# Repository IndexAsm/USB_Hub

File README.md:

# USB Hub

## Overview
A 4 port USB Hub.

## USB Version
It support USB 2.0 and older

## Max Current
It can supply up to 500mA per port <b>only when powered from USB-C compatible supply</b>. If the host port is connected to USB-A via USB-A USB-C cable it will only supply 100mA per port, to not exceed 500mA total.

## Hardware

It has a USB-C input and 4 USB-A output ports. Every port has ESD protection.

It uses USB2514 as the main IC.

Everything is placed on a 4-layer board.

## BOM

| Reference                                                                | Qty | Value            | Link                                                                                             | Footprint                                              |
|--------------------------------------------------------------------------|-----|------------------|--------------------------------------------------------------------------------------------------|--------------------------------------------------------|
| C1,C3,C4,C6,C7,C8,C9,C10,C11,C12,C13,C17,C18,C22,C23,C24,C25,C28,C29,C44 | 20  | 100n             |                                                                                                  | Capacitor_SMD:C_0603_1608Metric                        |
| C2,C5,C14,C15,C16,C19,C20,C21,C30                                        | 9   | 2u2              |                                                                                                  | Capacitor_SMD:C_0603_1608Metric                        |
| C34,C35                                                                  | 2   | 8p               | https://www.tme.eu/pl/details/cga3e2c0g1h080daa/kondensatory-mlcc-smd/tdk/cga3e2c0g1h080d080aa/  | Capacitor_SMD:C_0603_1608Metric                        |
| C57,C58                                                                  | 2   | 22u              | https://www.tme.eu/pl/details/grm31cr61e226ke15l/kondensatory-mlcc-smd/murata/                   | Capacitor_SMD:C_1206_3216Metric                        |
| J1,J2,J3,J4                                                              | 4   | USB_A            |                                                                                                  | USB-A-S-X-X-VT:USB-A-S-X-X-VT                          |
| J12                                                                      | 1   | USB4105-GF-A-120 | https://www.tme.eu/pl/details/usb4105-gf-a-120/zlacza-usb-i-ieee1394/gct/                        | Connector_USB:USB_C_Receptacle_G-Switch_GT-USB-7010ASV |
| R1,R2,R3,R4,R5,R6,R7,R8,R9,R10,R11                                       | 11  | 100k             |                                                                                                  | Resistor_SMD:R_0603_1608Metric                         |
| R12                                                                      | 1   | 12k              |                                                                                                  | Resistor_SMD:R_0603_1608Metric                         |
| R33,R34                                                                  | 2   | 5k1              |                                                                                                  | Resistor_SMD:R_0603_1608Metric                         |
| R36                                                                      | 1   | 1M               |                                                                                                  | Resistor_SMD:R_0603_1608Metric                         |
| U1                                                                       | 1   | USB2514B_Bi      | https://www.tme.eu/pl/details/usb2514b-aezc/uklady-scalone-interfejs-usb/microchip-technology/   | Package_DFN_QFN:QFN-36-1EP_6x6mm_P0.5mm_EP3.7x3.7mm    |
| U2,U3                                                                    | 2   | MIC2026-1xM      | https://www.tme.eu/pl/details/mic2026-1ym/power-switches-uklady-scalone/microchip-technology/    | Package_SO:SOIC-8_3.9x4.9mm_P1.27mm                    |
| U4,U5,U6,U7,U8                                                           | 5   | USBLC6-2SC6      |                                                                                                  | Package_TO_SOT_SMD:SOT-23-6                            |
| U9                                                                       | 1   | AMS1117-3.3      |                                                                                                  | Package_TO_SOT_SMD:SOT-223-3_TabPin2                   |
| Y1                                                                       | 1   | Crystal_GND24    | https://www.tme.eu/pl/en/details/3225-24m-sr/resonators-and-generators/sr-passives/wtl3m23500rh/ | Crystal:Crystal_SMD_EuroQuartz_MT-4Pin_3.2x2.5mm       |
| PCB                                                                      | 1   |                  | https://jlcpcb.com/                                                                              |                                                        |

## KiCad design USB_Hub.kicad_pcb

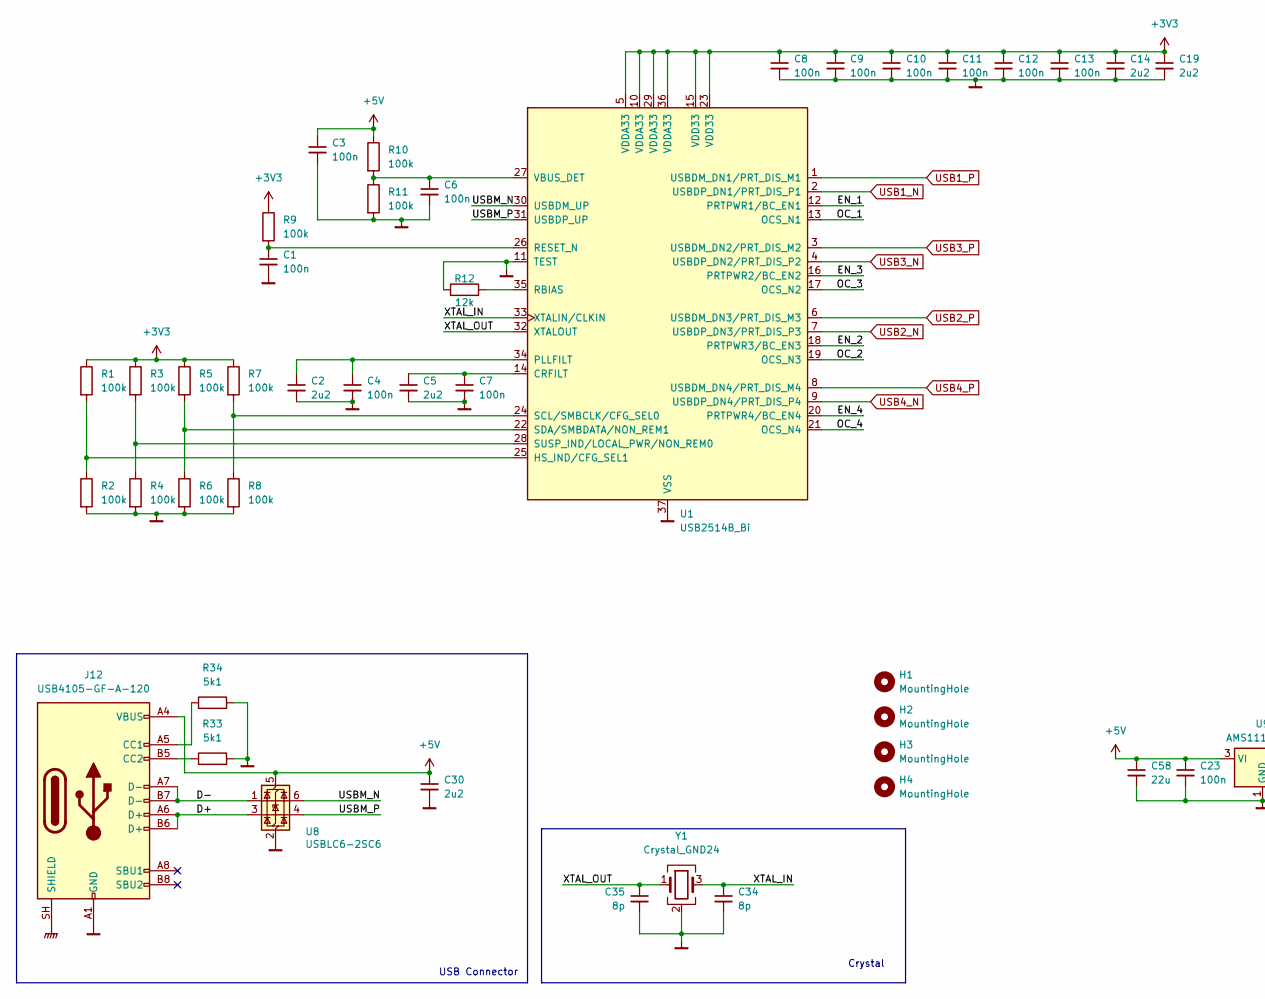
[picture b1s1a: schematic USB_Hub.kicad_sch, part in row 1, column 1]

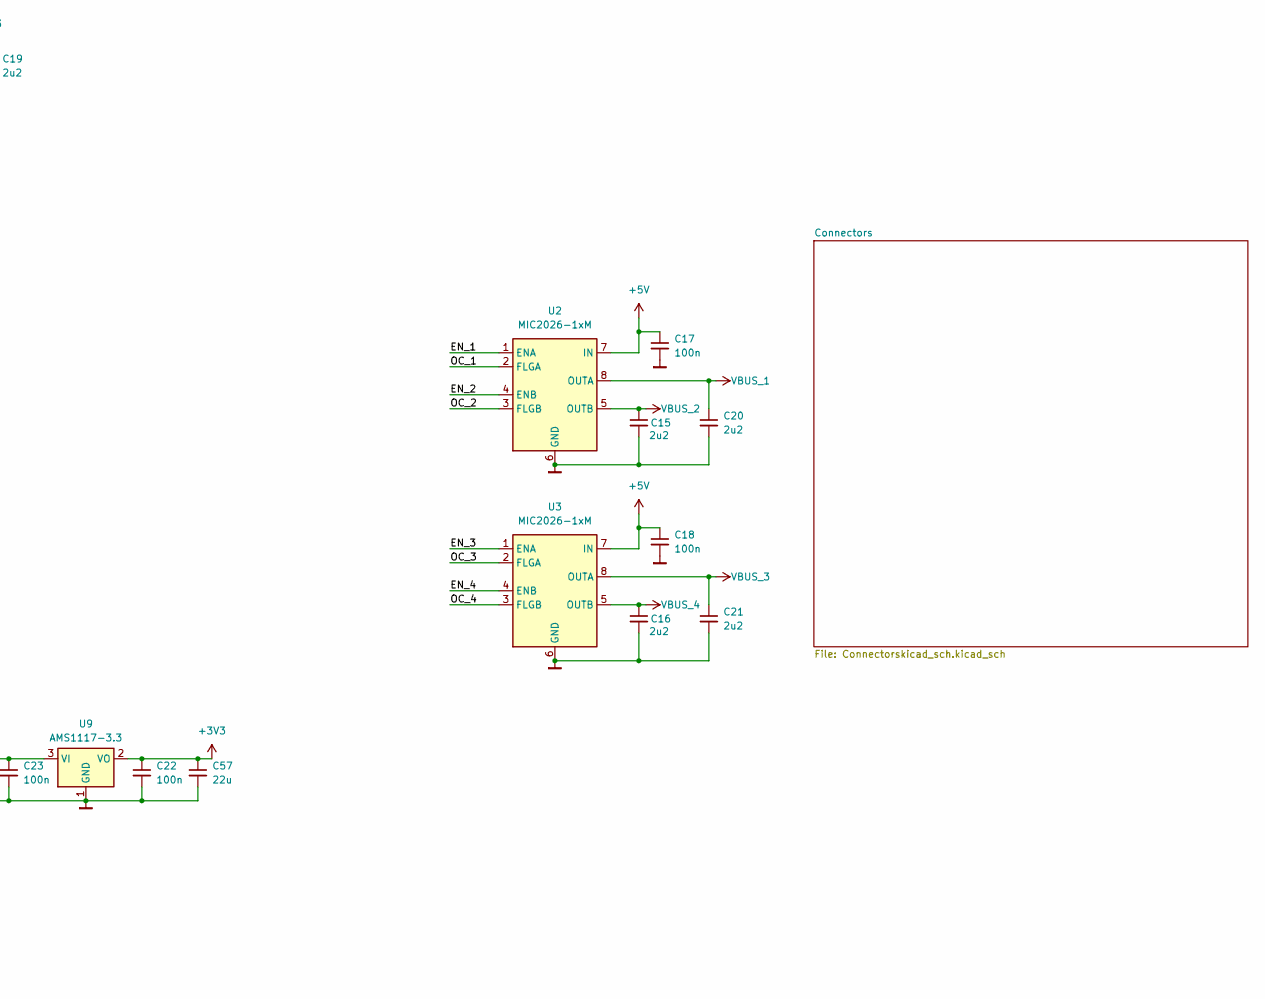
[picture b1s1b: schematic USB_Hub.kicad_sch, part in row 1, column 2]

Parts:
C1, C3, C4, C6, C7, C8, C9, C10, C11, C12, C13, C17, C18, C22, C23: 100n; C_0603_1608Metric
C2, C5, C14, C15, C16, C19, C20, C21, C30: 2u2; C_0603_1608Metric
C34, C35: 8p; C_0603_1608Metric
C57, C58: 22u; C_1206_3216Metric
H1, H2, H3, H4: MountingHole; MountingHole_3.2mm_M3
J12: USB4105-GF-A-120; USB_C_Receptacle_G-Switch_GT-USB-7010ASV
R1, R2, R3, R4, R5, R6, R7, R8, R9, R10, R11: 100k; R_0603_1608Metric
R12: 12k; R_0603_1608Metric
R33, R34: 5k1; R_0603_1608Metric
U1: USB2514B_Bi; QFN-36-1EP_6x6mm_P0.5mm_EP3.7x3.7mm
U2, U3: MIC2026-1xM; SOIC-8_3.9x4.9mm_P1.27mm
U8: USBLC6-2SC6; SOT-23-6
U9: AMS1117-3.3; SOT-223-3_TabPin2
Y1: Crystal_GND24; Crystal_SMD_EuroQuartz_MT-4Pin_3.2x2.5mm

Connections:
+3V3: C8.1, C9.1, C10.1, C11.1, C12.1, C13.1, C14.1, C19.1, C22.1, C57.1, R1.1, R3.1, R5.1, R7.1, R9.1, U1.5 (VDDA33), U1.10 (VDDA33), U1.15 (VDD33), U1.23 (VDD33), U1.29 (VDDA33), U1.36 (VDDA33), U9.2 (VO)
+5V: C3.1, C17.1, C18.1, C23.1, C30.1, C58.1, J12.A4 (VBUS), J12.A9 (VBUS), J12.B4 (VBUS), J12.B9 (VBUS), R10.1, U2.7 (IN), U3.7 (IN), U8.5 (VBUS), U9.3 (VI)
/D+: J12.A6 (D+), J12.B6 (D+), U8.3 (I/O2)
/D-: J12.A7 (D-), J12.B7 (D-), U8.1 (I/O1)
/EN_1: U1.12 (PRTPWR1/BC_EN1), U2.1 (ENA)
/EN_2: U1.18 (PRTPWR3/BC_EN3), U2.4 (ENB)
/EN_3: U1.16 (PRTPWR2/BC_EN2), U3.1 (ENA)
/EN_4: U1.20 (PRTPWR4/BC_EN4), U3.4 (ENB)
/OC_1: U1.13 (OCS_N1), U2.2 (FLGA)
/OC_2: U1.19 (OCS_N3), U2.3 (FLGB)
/OC_3: U1.17 (OCS_N2), U3.2 (FLGA)
/OC_4: U1.21 (OCS_N4), U3.3 (FLGB)
/USBM_N: U1.30 (USBDM_UP), U8.6 (I/O1)
/USBM_P: U1.31 (USBDP_UP), U8.4 (I/O2)
/XTAL_IN: C34.1, U1.33 (XTALIN/CLKIN), Y1.3
/XTAL_OUT: C35.1, U1.32 (XTALOUT), Y1.1
GNDPWR: J12.SH (SHIELD); also elsewhere on the board
Masa: C1.2, C2.2, C3.2, C4.2, C5.2, C6.2, C7.2, C8.2, C9.2, C10.2, C11.2, C12.2, C13.2, C14.2, C15.2, C16.2, C17.2, C18.2, C19.2, C20.2, C21.2, C22.2, C23.2, C30.2, C34.2, C35.2, C57.2, C58.2, J12.A1 (GND), J12.A12 (GND), J12.B1 (GND), J12.B12 (GND), R2.2, R4.2, R6.2, R8.2, R11.2, R12.1, R33.2, R34.2, U1.11 (TEST), U1.37 (VSS), U2.6 (GND), U3.6 (GND), U8.2 (GND), U9.1 (GND), Y1.2 (G), Y1.4 (G); also elsewhere on the board
unnamed: J12.A5 (CC1), R34.1
unnamed: J12.B5 (CC2), R33.1
unnamed: C5.1, C7.1, U1.14 (CRFILT)
unnamed: R1.2, R2.1, U1.25 (HS_IND/CFG_SEL1)
unnamed: C2.1, C4.1, U1.34 (PLLFILT)
unnamed: R12.2, U1.35 (RBIAS)
unnamed: C1.1, R9.2, U1.26 (RESET_N)
unnamed: R7.2, R8.1, U1.24 (SCL/SMBCLK/CFG_SEL0)
unnamed: R5.2, R6.1, U1.22 (SDA/SMBDATA/NON_REM1)
unnamed: R3.2, R4.1, U1.28 (SUSP_IND/LOCAL_PWR/NON_REM0)
unnamed: C6.1, R10.2, R11.1, U1.27 (VBUS_DET)
USB1_N: U1.2 (USBDP_DN1/PRT_DIS_P1); also elsewhere on the board
USB1_P: U1.1 (USBDM_DN1/PRT_DIS_M1); also elsewhere on the board
USB2_N: U1.7 (USBDP_DN3/PRT_DIS_P3); also elsewhere on the board
USB2_P: U1.6 (USBDM_DN3/PRT_DIS_M3); also elsewhere on the board
USB3_N: U1.4 (USBDP_DN2/PRT_DIS_P2); also elsewhere on the board
USB3_P: U1.3 (USBDM_DN2/PRT_DIS_M2); also elsewhere on the board
USB4_N: U1.9 (USBDP_DN4/PRT_DIS_P4); also elsewhere on the board
USB4_P: U1.8 (USBDM_DN4/PRT_DIS_M4); also elsewhere on the board
VBUS_1: C20.1, U2.8 (OUTA); also elsewhere on the board
VBUS_2: C15.1, U2.5 (OUTB); also elsewhere on the board
VBUS_3: C21.1, U3.8 (OUTA); also elsewhere on the board
VBUS_4: C16.1, U3.5 (OUTB); also elsewhere on the board

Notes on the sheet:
USB Connector
Crystal

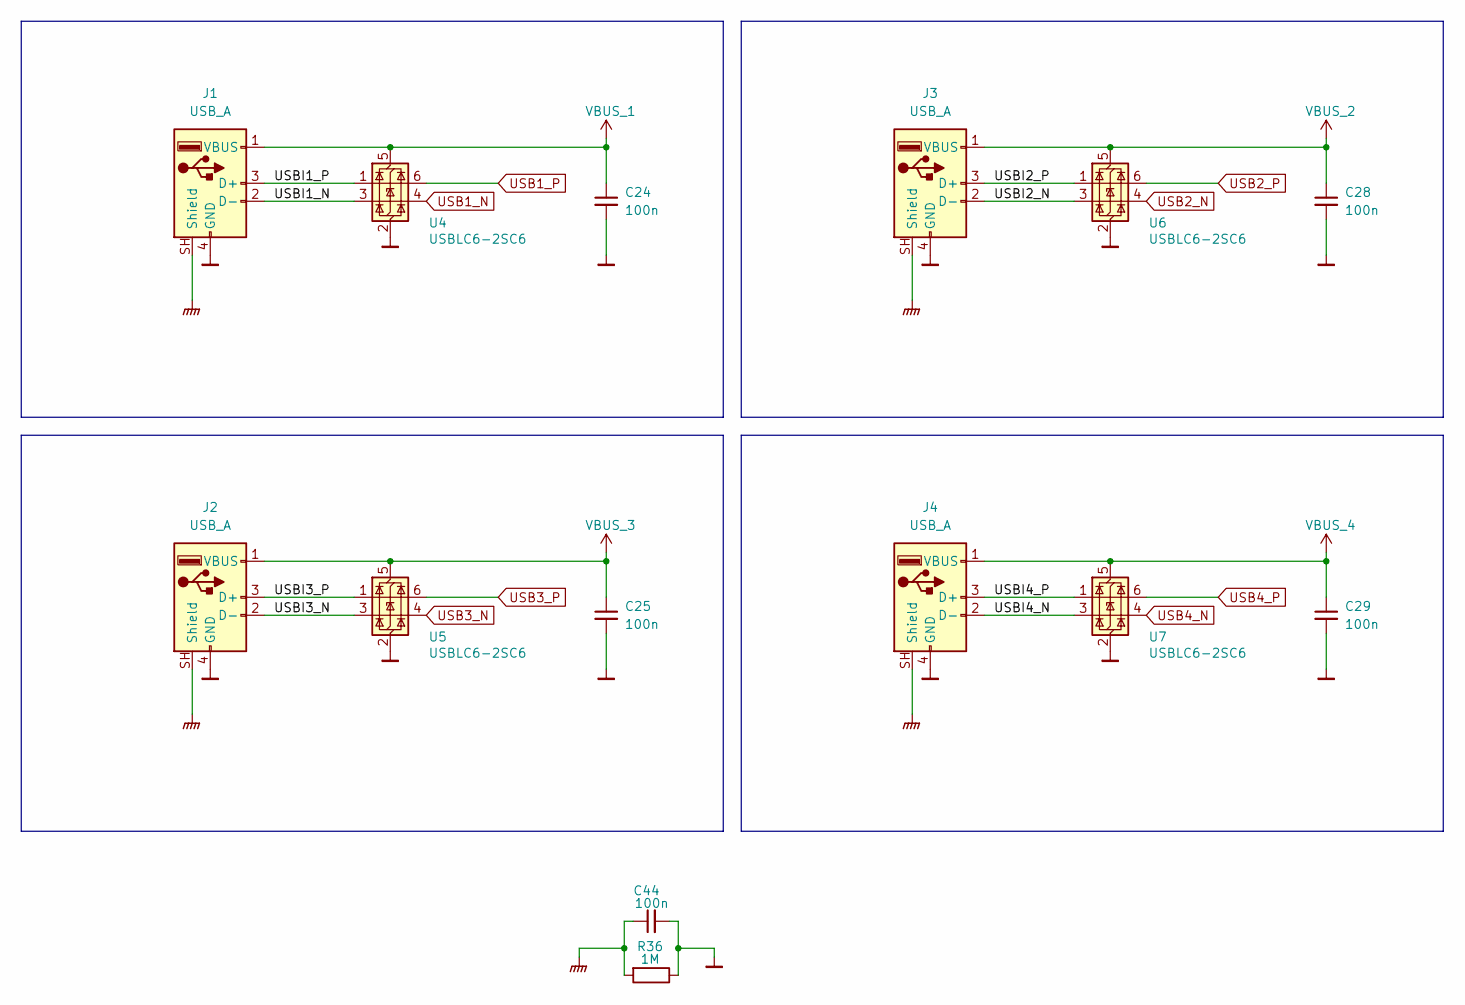
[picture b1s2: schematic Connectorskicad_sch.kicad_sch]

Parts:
C24, C25, C28, C29, C44: 100n; C_0603_1608Metric
J1, J2, J3, J4: USB_A; USB-A-S-X-X-VT
R36: 1M; R_0603_1608Metric
U4, U5, U6, U7: USBLC6-2SC6; SOT-23-6

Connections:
/Connectors/USBI1_N: J1.2 (D-), U4.3 (I/O2)
/Connectors/USBI1_P: J1.3 (D+), U4.1 (I/O1)
/Connectors/USBI2_N: J3.2 (D-), U6.3 (I/O2)
/Connectors/USBI2_P: J3.3 (D+), U6.1 (I/O1)
/Connectors/USBI3_N: J2.2 (D-), U5.3 (I/O2)
/Connectors/USBI3_P: J2.3 (D+), U5.1 (I/O1)
/Connectors/USBI4_N: J4.2 (D-), U7.3 (I/O2)
/Connectors/USBI4_P: J4.3 (D+), U7.1 (I/O1)
GNDPWR: C44.1, J1.SH (Shield), J2.SH (Shield), J3.SH (Shield), J4.SH (Shield), R36.2; also elsewhere on the board
Masa: C24.2, C25.2, C28.2, C29.2, C44.2, J1.4 (GND), J2.4 (GND), J3.4 (GND), J4.4 (GND), R36.1, U4.2 (GND), U5.2 (GND), U6.2 (GND), U7.2 (GND); also elsewhere on the board
USB1_N: U4.4 (I/O2); also elsewhere on the board
USB1_P: U4.6 (I/O1); also elsewhere on the board
USB2_N: U6.4 (I/O2); also elsewhere on the board
USB2_P: U6.6 (I/O1); also elsewhere on the board
USB3_N: U5.4 (I/O2); also elsewhere on the board
USB3_P: U5.6 (I/O1); also elsewhere on the board
USB4_N: U7.4 (I/O2); also elsewhere on the board
USB4_P: U7.6 (I/O1); also elsewhere on the board
VBUS_1: C24.1, J1.1 (VBUS), U4.5 (VBUS); also elsewhere on the board
VBUS_2: C28.1, J3.1 (VBUS), U6.5 (VBUS); also elsewhere on the board
VBUS_3: C25.1, J2.1 (VBUS), U5.5 (VBUS); also elsewhere on the board
VBUS_4: C29.1, J4.1 (VBUS), U7.5 (VBUS); also elsewhere on the board

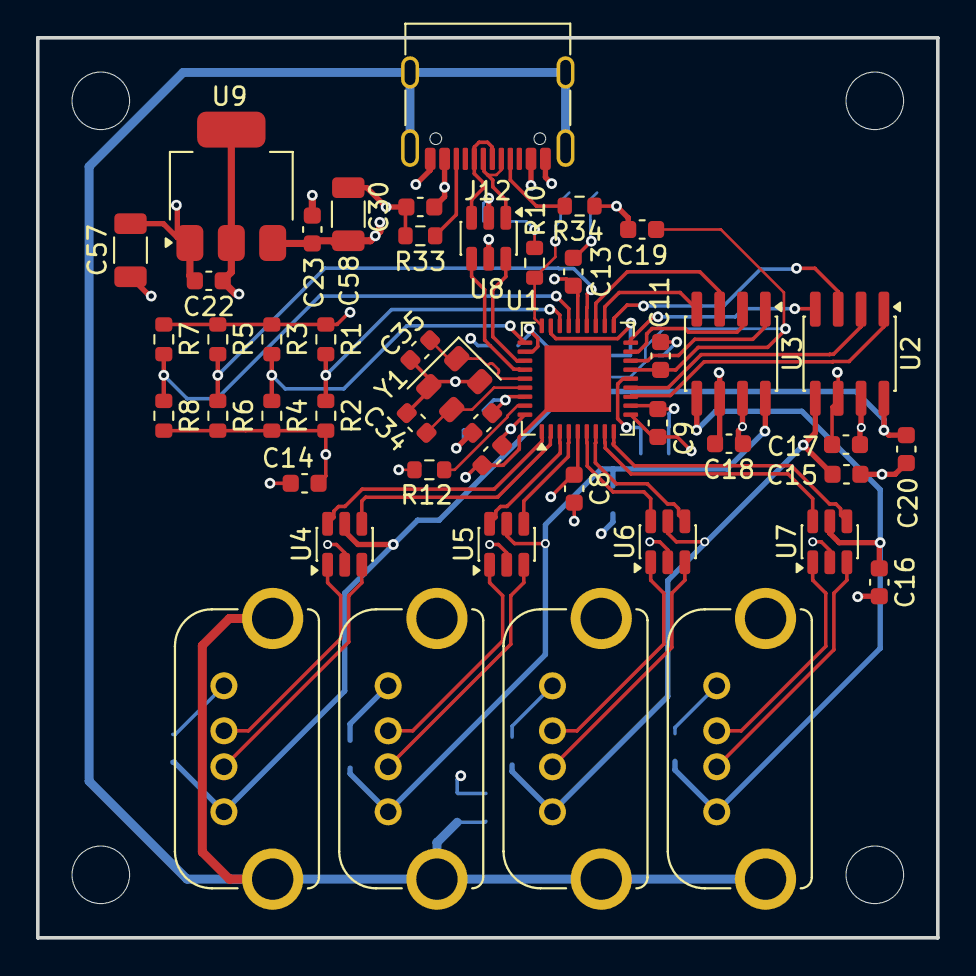
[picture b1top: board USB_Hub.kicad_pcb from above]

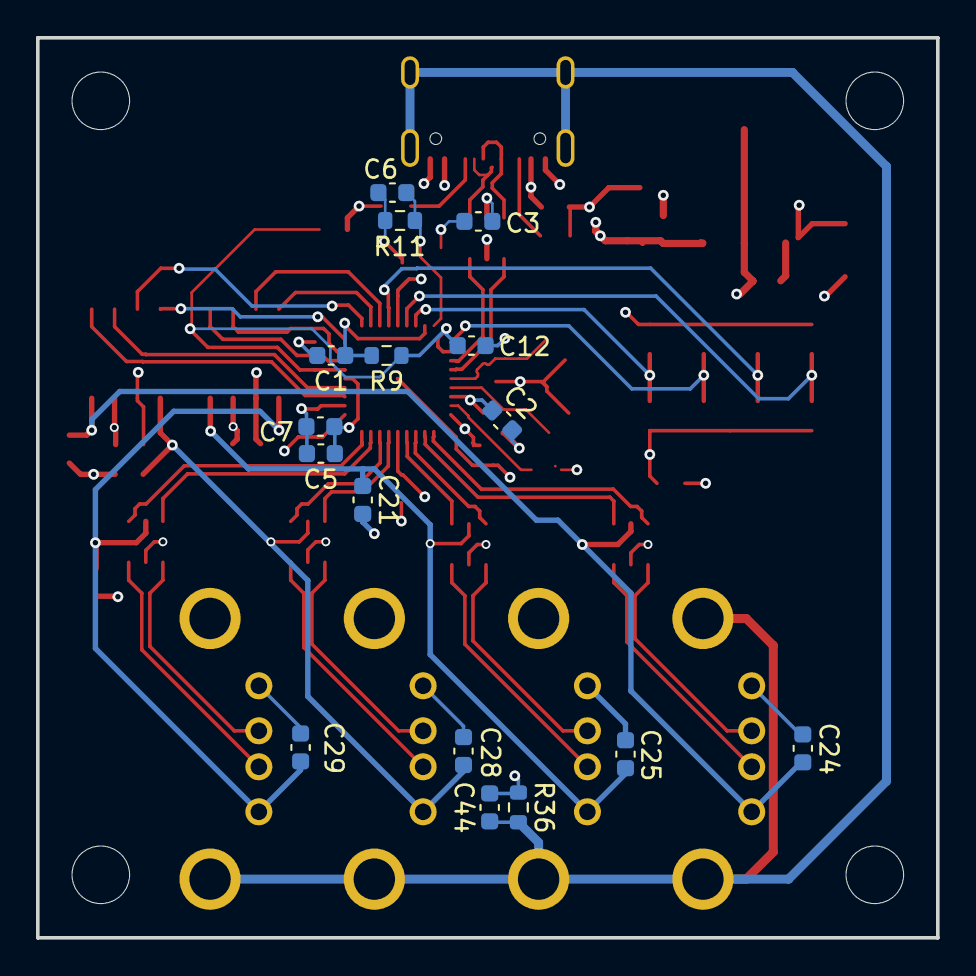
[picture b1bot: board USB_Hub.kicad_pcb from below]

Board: 4 copper layers, 50.0 x 50.0 mm, 67 parts (16 on the bottom side), 49 nets.

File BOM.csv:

Reference,Qty,Value,Link,DNP,Footprint
"C1,C3,C4,C6,C7,C8,C9,C10,C11,C12,C13,C17,C18,C22,C23,C24,C25,C28,C29,C44",20,100n,,,Capacitor_SMD:C_0603_1608Metric
"C2,C5,C14,C15,C16,C19,C20,C21,C30",9,2u2,,,Capacitor_SMD:C_0603_1608Metric
"C34,C35",2,8p,https://www.tme.eu/pl/details/cga3e2c0g1h080daa/kondensatory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,,Capacitor_SMD:C_0603_1608Metric
"C57,C58",2,22u,https://www.tme.eu/pl/details/grm31cr61e226ke15l/kondensator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,,Capacitor_SMD:C_1206_3216Metric
"J1,J2,J3,J4",4,USB_A,,,USB-A-S-X-X-VT:USB-A-S-X-X-VT
J12,1,USB4105-GF-A-120,https://www.tme.eu/pl/details/usb4105-gf-a-120/zlacza-usb-i-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,,Connector_USB:USB_C_Receptacle_G-Switch_GT-USB-7010ASV
"R1,R2,R3,R4,R5,R6,R7,R8,R9,R10,R11",11,100k,,,Resistor_SMD:R_0603_1608Metric
R12,1,12k,,,Resistor_SMD:R_0603_1608Metric
"R33,R34",2,5k1,,,Resistor_SMD:R_0603_1608Metric
R36,1,1M,,,Resistor_SMD:R_0603_1608Metric
U1,1,USB2514B_Bi,https://www.tme.eu/pl/details/usb2514b-aezc/uklady-scalone-i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,,Package_DFN_QFN:QFN-36-1EP_6x6mm_P0.5mm_EP3.7x3.7mm
"U2,U3",2,MIC2026-1xM,https://www.tme.eu/pl/details/mic2026-1ym/power-switches-ukl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,,Package_SO:SOIC-8_3.9x4.9mm_P1.27mm
"U4,U5,U6,U7,U8",5,USBLC6-2SC6,,,Package_TO_SOT_SMD:SOT-23-6
U9,1,AMS1117-3.3,,,Package_TO_SOT_SMD:SOT-223-3_TabPin2
Y1,1,Crystal_GND24,https://www.tme.eu/pl/en/details/3225-24m-sr/resonators-and-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,,Crystal:Crystal_SMD_EuroQuartz_MT-4Pin_3.2x2.5mm
PCB,1,,https://jlcpcb.com/
